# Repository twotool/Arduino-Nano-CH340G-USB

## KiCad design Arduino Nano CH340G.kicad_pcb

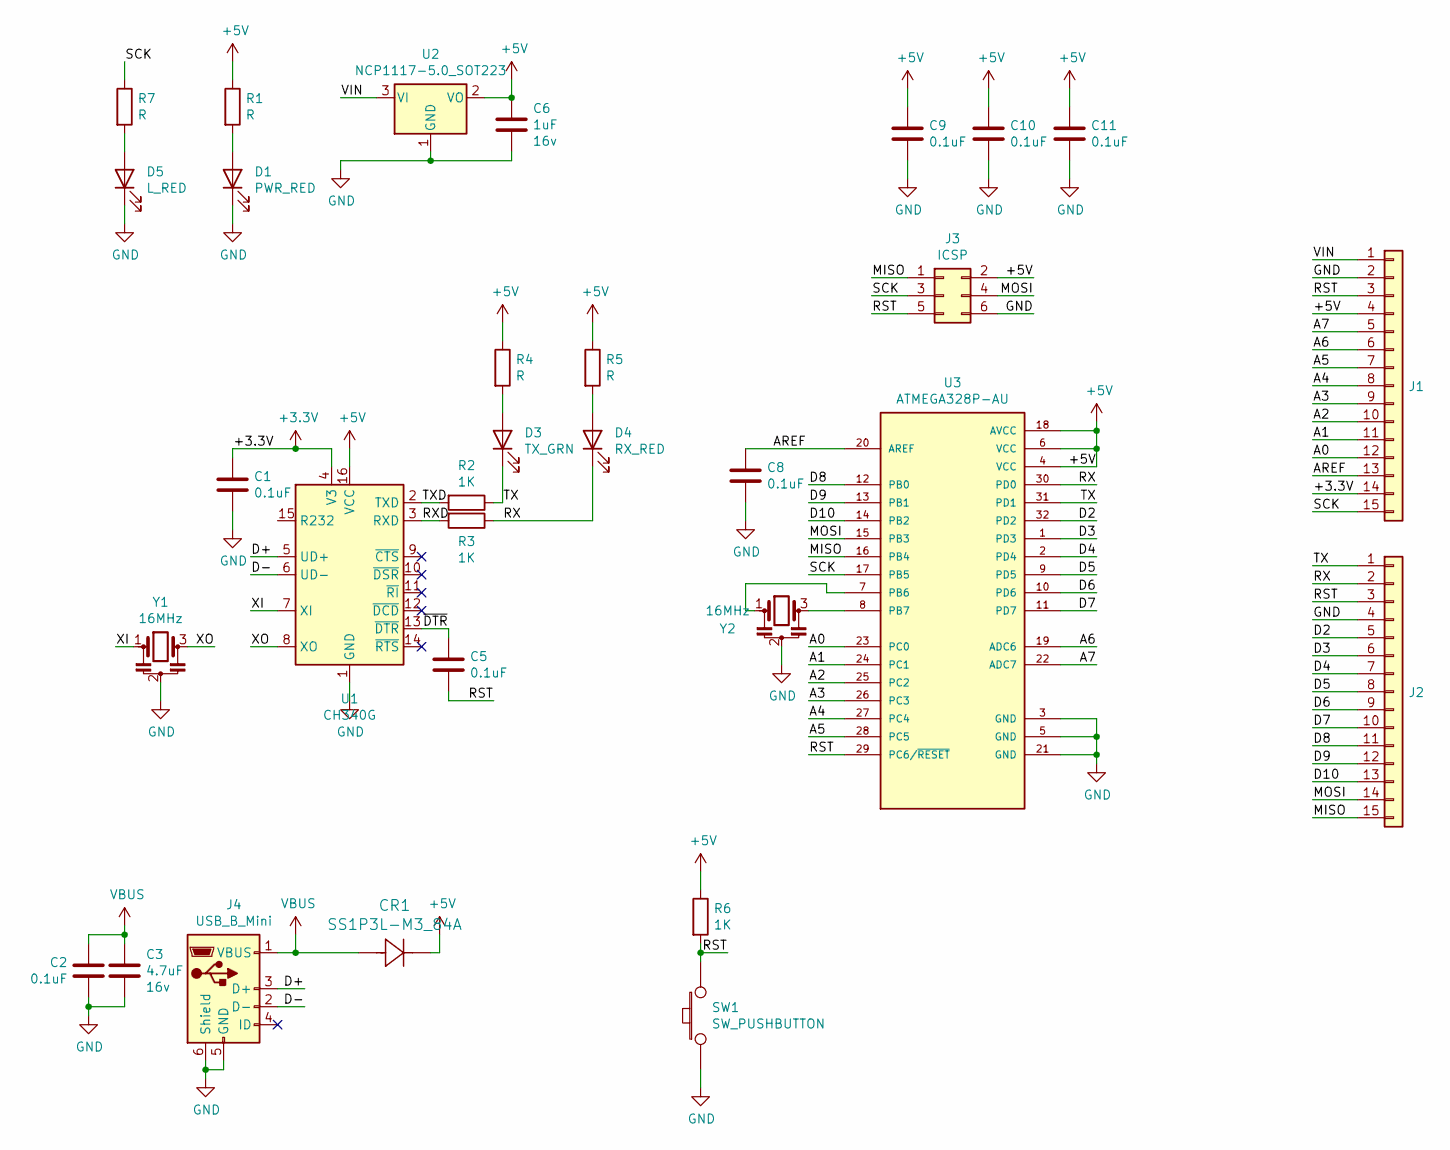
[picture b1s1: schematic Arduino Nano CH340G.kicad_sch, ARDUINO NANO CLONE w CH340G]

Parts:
C1, C2, C5, C8, C9, C10, C11: 0.1uF; C_0402_1005Metric
C3: 4.7uF; C_1206_3216Metric_Pad1.33x1.80mm_HandSolder; Rated Voltage 16v
C6: 1uF; C_1206_3216Metric; Rated Voltage 16v
CR1: SS1P3L-M3_84A
D1: PWR_RED; LED_0603_1608Metric_Pad1.05x0.95mm_HandSolder
D3: TX_GRN; LED_0603_1608Metric_Pad1.05x0.95mm_HandSolder
D4: RX_RED; LED_0603_1608Metric_Pad1.05x0.95mm_HandSolder
D5: L_RED; LED_0603_1608Metric_Pad1.05x0.95mm_HandSolder
J1, J2: Conn_01x15; PinHeader_1x15_P2.54mm_Vertical
J3: ICSP; PinHeader_2x03_P2.54mm_Vertical
J4: USB_B_Mini; USB_Mini-B_Lumberg_2486_01_Horizontal
R1, R4, R5, R7: R; R_0402_1005Metric_Pad0.72x0.64mm_HandSolder
R2, R3, R6: 1K; R_0402_1005Metric_Pad0.72x0.64mm_HandSolder
SW1: SW_PUSHBUTTON; SW_SPST_CK_RS282G05A3
U1: CH340G; SOIC-16_3.9x9.9mm_P1.27mm
U2: NCP1117-5.0_SOT223; SOT-223-3_TabPin2
U3: ATMEGA328P-AU
Y1, Y2: 16MHz; Resonator_SMD_Murata_CSTxExxV-3Pin_3.0x1.1mm

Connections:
+3V3: C1.1, J1.14, U1.4 (V3)
+5V: C6.1, C9.1, C10.1, C11.1, CR1.1, J1.4, J3.2, R1.1, R4.1, R5.1, R6.1, U1.16 (VCC), U2.2 (VO), U3.4 (VCC), U3.6 (VCC), U3.18 (AVCC)
/A0: J1.12, U3.23 (PC0)
/A1: J1.11, U3.24 (PC1)
/A2: J1.10, U3.25 (PC2)
/A3: J1.9, U3.26 (PC3)
/A4: J1.8, U3.27 (PC4)
/A5: J1.7, U3.28 (PC5)
/A6: J1.6, U3.19 (ADC6)
/A7: J1.5, U3.22 (ADC7)
/AREF: C8.1, J1.13, U3.20 (AREF)
/D2: J2.5, U3.32 (PD2)
/D3: J2.6, U3.1 (PD3)
/D4: J2.7, U3.2 (PD4)
/D5: J2.8, U3.9 (PD5)
/D6: J2.9, U3.10 (PD6)
/D7: J2.10, U3.11 (PD7)
/D8: J2.11, U3.12 (PB0)
/D9: J2.12, U3.13 (PB1)
/D10: J2.13, U3.14 (PB2)
/D+: J4.3 (D+), U1.5 (UD+)
/D-: J4.2 (D-), U1.6 (UD-)
/MISO: J2.15, J3.1, U3.16 (PB4)
/MOSI: J2.14, J3.4, U3.15 (PB3)
/RST: C5.2, J1.3, J2.3, J3.5, R6.2, SW1.2, U3.29 (PC6/~RESET)
/RX: D4.1 (K), J2.2, R3.1, U3.30 (PD0)
/RXD: R3.2, U1.3 (RXD)
/SCK: J1.15, J3.3, R7.1, U3.17 (PB5)
/TX: D3.1 (K), J2.1, R2.1, U3.31 (PD1)
/TXD: R2.2, U1.2 (TXD)
/VIN: J1.1, U2.3 (VI)
/XI: U1.7 (XI), Y1.1
/XO: U1.8 (XO), Y1.3
/~DTR: C5.1, U1.13 (~DTR)
GND: C1.2, C2.2, C3.2, C6.2, C8.2, C9.2, C10.2, C11.2, D1.1 (K), D5.1 (K), J1.2, J2.4, J3.6, J4.5 (GND), J4.6 (Shield), SW1.1, U1.1 (GND), U2.1 (GND), U3.3 (GND), U3.5 (GND), U3.21 (GND), Y1.2, Y2.2
unnamed: D1.2 (A), R1.2
unnamed: D3.2 (A), R4.2
unnamed: D4.2 (A), R5.2
unnamed: D5.2 (A), R7.2
unnamed: U3.7 (PB6), Y2.1
unnamed: U3.8 (PB7), Y2.3
VBUS: C2.1, C3.1, CR1.2, J4.1 (VBUS)

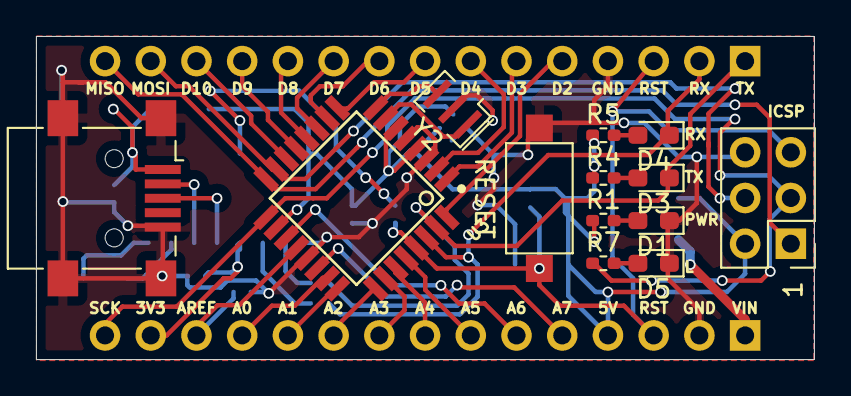
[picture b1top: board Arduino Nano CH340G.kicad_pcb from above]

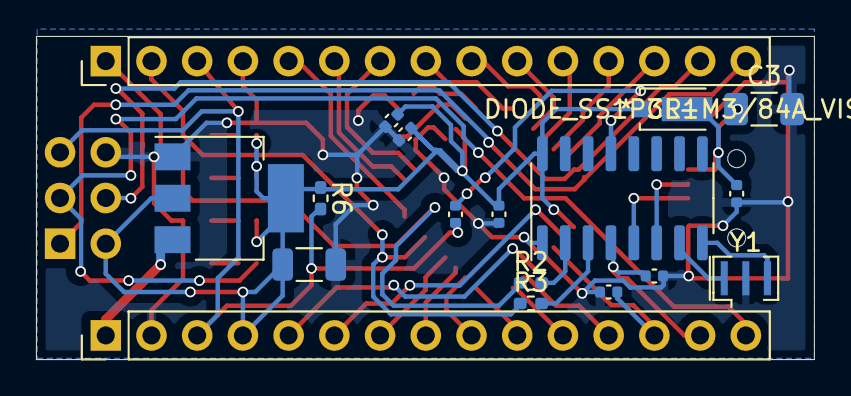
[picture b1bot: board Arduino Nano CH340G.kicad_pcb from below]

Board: 2 copper layers, 43.2 x 18.0 mm, 31 parts (18 on the bottom side), 42 nets.

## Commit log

2022-07-24 Arduino Nano CH340G USB mini version 1.0.0

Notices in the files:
parts and their libraries:
Copyright 2021 Accelerated Designs. All rights reserved.
